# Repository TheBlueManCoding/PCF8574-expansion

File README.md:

# PCF8574-expansion
I2C expansion board for the ModularControlPanel

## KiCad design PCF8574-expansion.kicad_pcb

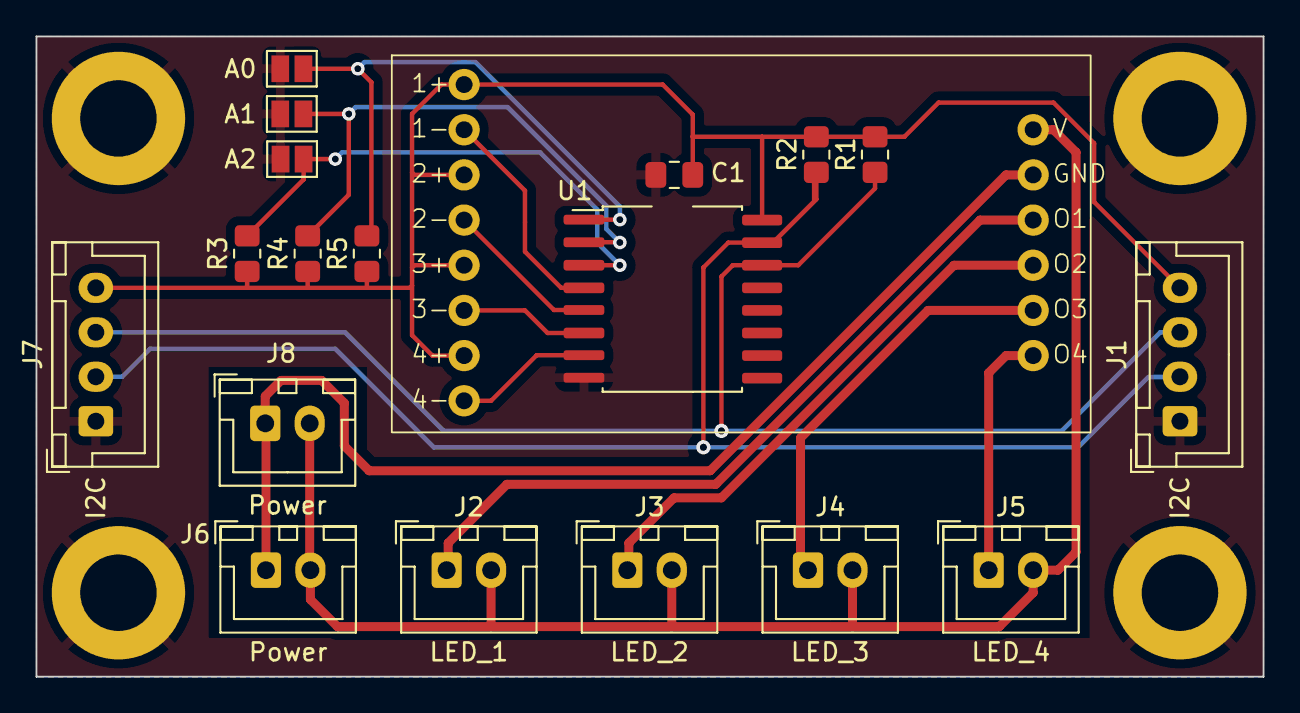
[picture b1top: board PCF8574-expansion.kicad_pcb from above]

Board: 2 copper layers, 69.0 x 36.0 mm, 23 parts (0 on the bottom side), 17 nets.

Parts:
C1: C; C_0805_2012Metric_Pad1.18x1.45mm_HandSolder
D1: OP714A04
H1, H2, H3, H4: MountingHole_Pad; MountingHole_4.3mm_M4_DIN965_Pad
J1, J7: I2C; JST_XH_B4B-XH-A_1x04_P2.50mm_Vertical
J2: LED_1; JST_XH_B2B-XH-A_1x02_P2.50mm_Vertical
J3: LED_2; JST_XH_B2B-XH-A_1x02_P2.50mm_Vertical
J4: LED_3; JST_XH_B2B-XH-A_1x02_P2.50mm_Vertical
J5: LED_4; JST_XH_B2B-XH-A_1x02_P2.50mm_Vertical
J6, J8: Power; JST_XH_B2B-XH-A_1x02_P2.50mm_Vertical
JP1: A0; SolderJumper-2_P1.3mm_Open_Pad1.0x1.5mm
JP2: A1; SolderJumper-2_P1.3mm_Open_Pad1.0x1.5mm
JP3: A2; SolderJumper-2_P1.3mm_Open_Pad1.0x1.5mm
R1, R2, R3, R4, R5: 10K; R_0805_2012Metric_Pad1.20x1.40mm_HandSolder
U1: PCF8574; SO-16_7,7x10.2mm_P1.27mm-PCF8574

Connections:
+24V: D1.14 (V), J2.2, J3.2, J4.2, J5.2, J6.2, J8.2
+VSW: C1.1, D1.1 (1+), D1.3 (2+), D1.5 (3+), D1.7 (4+), J1.4, J7.4, R1.2, R2.2, R3.1, R4.1, R5.1, U1.16 (VDD)
GND: C1.2, H1.1, H2.1, H3.1, H4.1, J1.1, J7.1, JP1.1 (A), JP2.1 (A), JP3.1 (A), U1.8 (VSS)
GND2: D1.13 (G), J6.1, J8.1
LED_1: D1.2 (1-), U1.4 (P0)
LED_1_24V: D1.12 (01), J2.1
LED_2: D1.4 (2-), U1.5 (P1)
LED_2_24V: D1.11 (02), J3.1
LED_3: D1.6 (3-), U1.6 (P2)
LED_3_24V: D1.10 (03), J4.1
LED_4: D1.8 (4-), U1.7 (P3)
LED_4_24V: D1.9 (04), J5.1
unnamed: JP1.2 (B), R5.2, U1.1 (A0)
unnamed: JP2.2 (B), R4.2, U1.2 (A1)
unnamed: JP3.2 (B), R3.2, U1.3 (A2)
SCL: J1.3, J7.3, R1.1, U1.14 (SCL)
SDA: J1.2, J7.2, R2.1, U1.15 (SDA)

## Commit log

2023-11-12 First version, address inputs are missing some pullups
2023-11-12 Added adress pullups
